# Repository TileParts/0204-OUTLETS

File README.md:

0204-OUTLETS
==========

引出并固定现有的开发板。

## 特性

1. 双排针并联，方便将信号继续转接到别的地方，如逻辑分析仪
2. 预留上拉或下拉电阻焊盘（0402 封装，需要连接 VCC 或 GND）

## 协议

[CERN-OHL-P-2.0](LICENSE)

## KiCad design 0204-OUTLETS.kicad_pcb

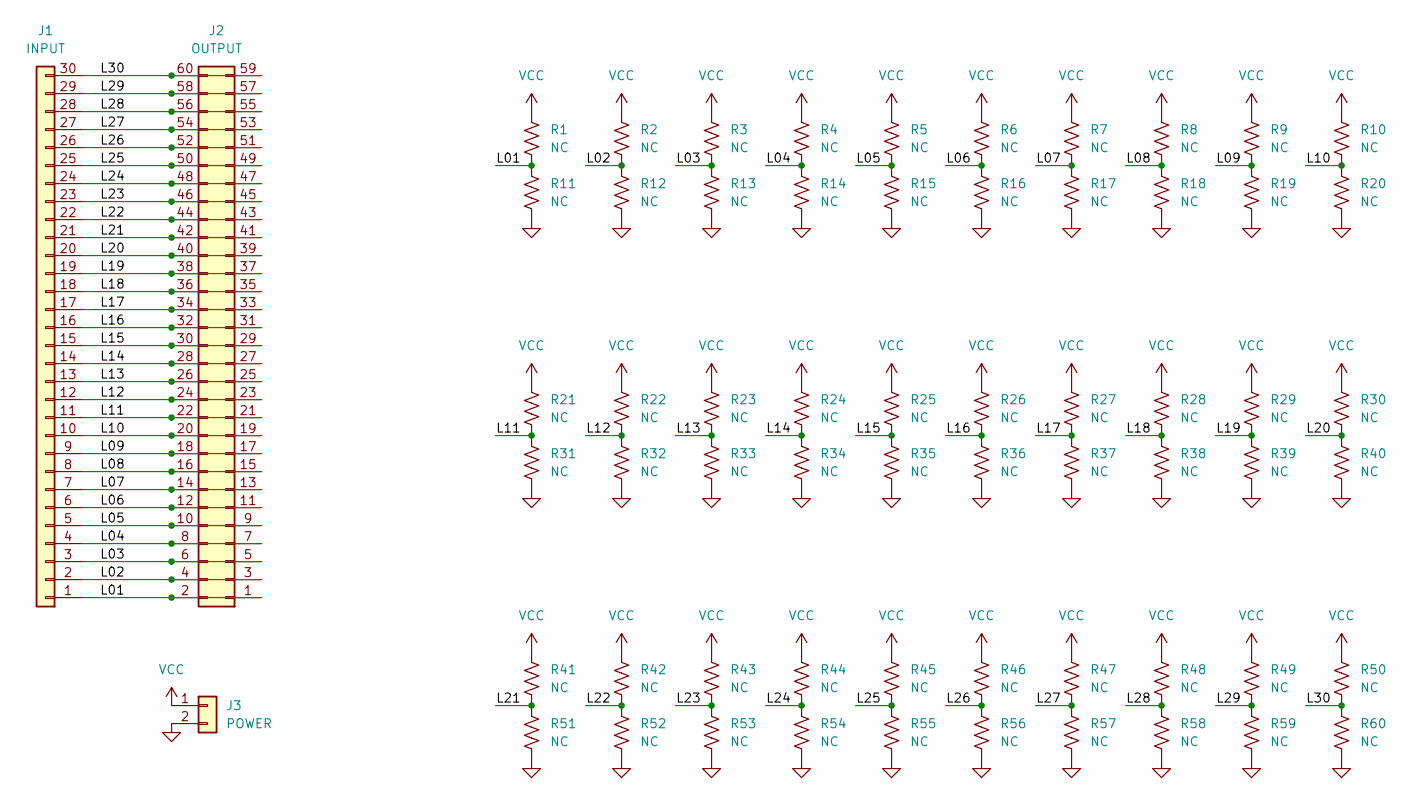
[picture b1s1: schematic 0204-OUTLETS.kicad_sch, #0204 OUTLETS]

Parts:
J1: INPUT; PinSocket_1x30_P2.54mm_Vertical
J2: OUTPUT; PinHeader_2x30_P2.54mm_Vertical
J3: POWER; PinHeader_1x02_P2.54mm_Vertical
R1, R2, R3, R4, R5, R6, R7, R8, R9, R10, R11, R12, R13, R14, R15, R16, R17, R18, R19, R20, R21, R22, R23, R24, R25, R26, R27, R28, R29, R30, R31, R32, R33, R34, R35, R36, R37, R38, R39, R40, R41, R42, R43, R44, R45, R46, R47, R48, R49, R50, R51, R52, R53, R54, R55, R56, R57, R58, R59, R60: NC; R_0402_1005Metric

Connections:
/L01: J1.1, J2.1, J2.2, R1.2, R11.1
/L02: J1.2, J2.3, J2.4, R2.2, R12.1
/L03: J1.3, J2.5, J2.6, R3.2, R13.1
/L04: J1.4, J2.7, J2.8, R4.2, R14.1
/L05: J1.5, J2.9, J2.10, R5.2, R15.1
/L06: J1.6, J2.11, J2.12, R6.2, R16.1
/L07: J1.7, J2.13, J2.14, R7.2, R17.1
/L08: J1.8, J2.15, J2.16, R8.2, R18.1
/L09: J1.9, J2.17, J2.18, R9.2, R19.1
/L10: J1.10, J2.19, J2.20, R10.2, R20.1
/L11: J1.11, J2.21, J2.22, R21.2, R31.1
/L12: J1.12, J2.23, J2.24, R22.2, R32.1
/L13: J1.13, J2.25, J2.26, R23.2, R33.1
/L14: J1.14, J2.27, J2.28, R24.2, R34.1
/L15: J1.15, J2.29, J2.30, R25.2, R35.1
/L16: J1.16, J2.31, J2.32, R26.2, R36.1
/L17: J1.17, J2.33, J2.34, R27.2, R37.1
/L18: J1.18, J2.35, J2.36, R28.2, R38.1
/L19: J1.19, J2.37, J2.38, R29.2, R39.1
/L20: J1.20, J2.39, J2.40, R30.2, R40.1
/L21: J1.21, J2.41, J2.42, R41.2, R51.1
/L22: J1.22, J2.43, J2.44, R42.2, R52.1
/L23: J1.23, J2.45, J2.46, R43.2, R53.1
/L24: J1.24, J2.47, J2.48, R44.2, R54.1
/L25: J1.25, J2.49, J2.50, R45.2, R55.1
/L26: J1.26, J2.51, J2.52, R46.2, R56.1
/L27: J1.27, J2.53, J2.54, R47.2, R57.1
/L28: J1.28, J2.55, J2.56, R48.2, R58.1
/L29: J1.29, J2.57, J2.58, R49.2, R59.1
/L30: J1.30, J2.59, J2.60, R50.2, R60.1
GND: J3.2, R11.2, R12.2, R13.2, R14.2, R15.2, R16.2, R17.2, R18.2, R19.2, R20.2, R31.2, R32.2, R33.2, R34.2, R35.2, R36.2, R37.2, R38.2, R39.2, R40.2, R51.2, R52.2, R53.2, R54.2, R55.2, R56.2, R57.2, R58.2, R59.2, R60.2
VCC: J3.1, R1.1, R2.1, R3.1, R4.1, R5.1, R6.1, R7.1, R8.1, R9.1, R10.1, R21.1, R22.1, R23.1, R24.1, R25.1, R26.1, R27.1, R28.1, R29.1, R30.1, R41.1, R42.1, R43.1, R44.1, R45.1, R46.1, R47.1, R48.1, R49.1, R50.1

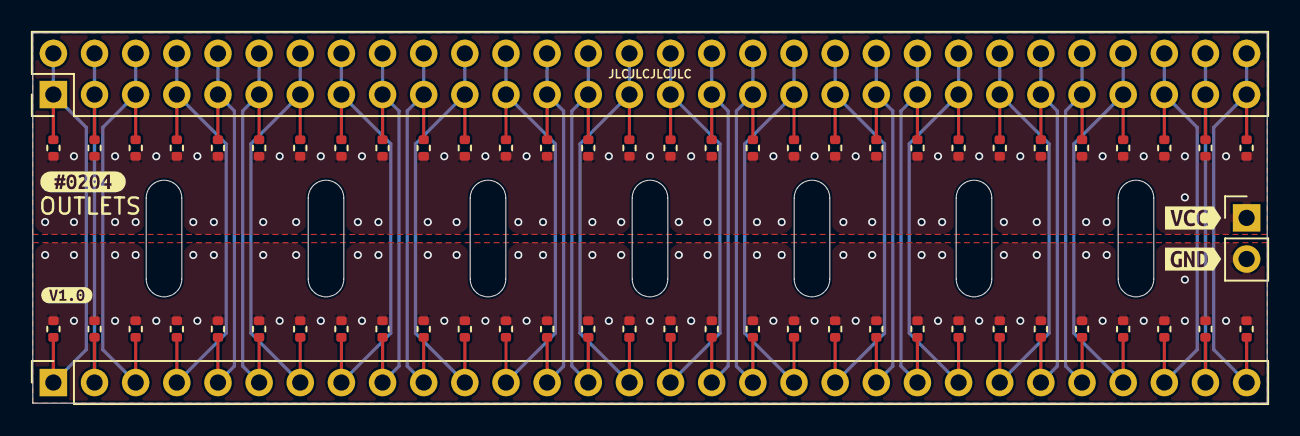
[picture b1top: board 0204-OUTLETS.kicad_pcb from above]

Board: 2 copper layers, 76.2 x 22.9 mm, 67 parts (0 on the bottom side), 32 nets.

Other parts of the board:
kibuzzard-634D0629: G***; kibuzzard-634D0629
kibuzzard-634D0633: G***; kibuzzard-634D0633
kibuzzard-634E0ED5: G***; kibuzzard-634E0ED5
kibuzzard-63351CB9: G***; kibuzzard-63351CB9

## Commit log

2022-10-18 Make outlet board
2022-10-18 Output gerber
2022-10-19 Add README
